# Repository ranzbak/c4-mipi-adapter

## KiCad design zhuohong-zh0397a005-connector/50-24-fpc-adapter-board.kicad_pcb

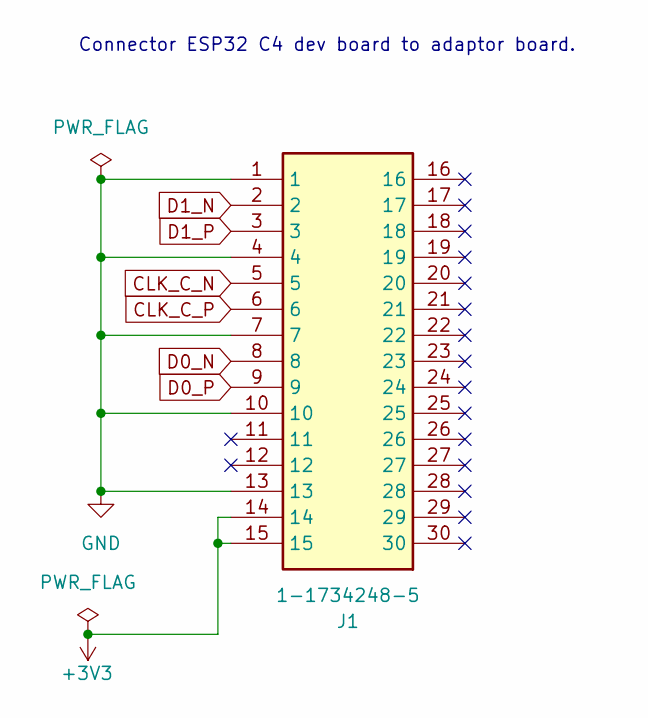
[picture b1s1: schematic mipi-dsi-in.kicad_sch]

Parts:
J1: 1-1734248-5; 117342485; Mouser Part Number 571-1-1734248-5

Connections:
+3V3: J1.14, J1.15; also elsewhere on the board
CLK_C_N: J1.5; also elsewhere on the board
CLK_C_P: J1.6; also elsewhere on the board
D0_N: J1.8; also elsewhere on the board
D0_P: J1.9; also elsewhere on the board
D1_N: J1.2; also elsewhere on the board
D1_P: J1.3; also elsewhere on the board
GND: J1.1, J1.4, J1.7, J1.10, J1.13; also elsewhere on the board

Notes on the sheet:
Connector ESP32 C4 dev board to adaptor board.

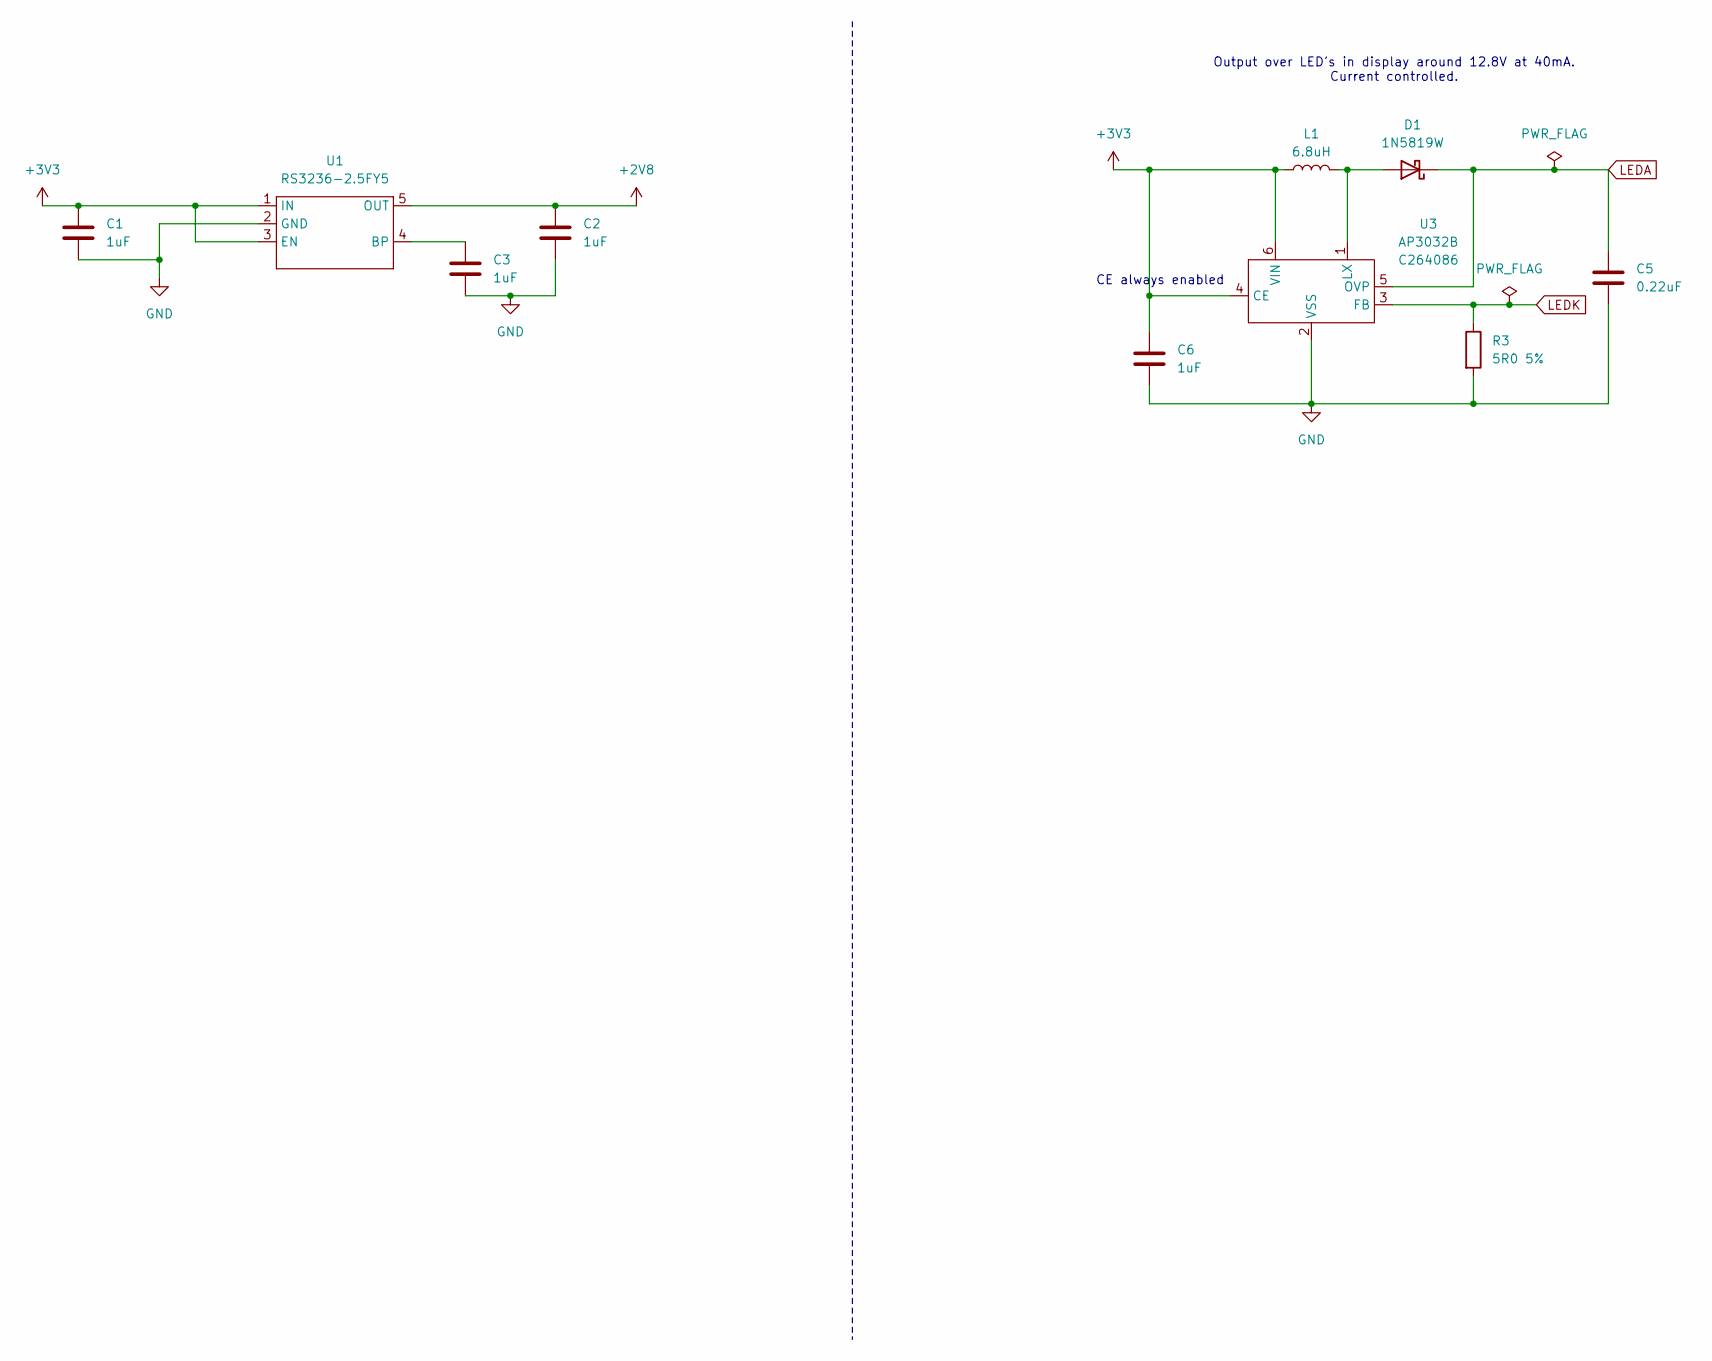
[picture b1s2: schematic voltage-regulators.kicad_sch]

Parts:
C1, C2, C3, C6: 1uF; C_0603_1608Metric; LCSC C386149
C5: 0.22uF; C_0603_1608Metric
D1: 1N5819W; D_SOD-123; LCSC C402219
L1: 6.8uH; L_1210_3225Metric; LCSC C394999
R3: 5R0 5%; R_0603_1608Metric; LCSC C2907176
U1: RS3236-2.5FY5; SOT-23-5; LCSC C379345
U3: AP3032B; SOT-23-6; LCSC C264086

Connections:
+2V8: C2.1, U1.5 (OUT); also elsewhere on the board
+3V3: C1.1, C6.1, L1.1, U1.1 (IN), U1.3 (EN), U3.4 (CE), U3.6 (VIN); also elsewhere on the board
GND: C1.2, C2.2, C3.2, C5.2, C6.2, R3.2, U1.2 (GND), U3.2 (VSS); also elsewhere on the board
LEDA: C5.1, D1.1 (K), U3.5 (OVP); also elsewhere on the board
LEDK: R3.1, U3.3 (FB); also elsewhere on the board
unnamed: D1.2 (A), L1.2, U3.1 (LX)
unnamed: C3.1, U1.4 (BP)

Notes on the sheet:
CE always enabled
Output over LED's in display around 12.8V at 40mA. Current controlled.

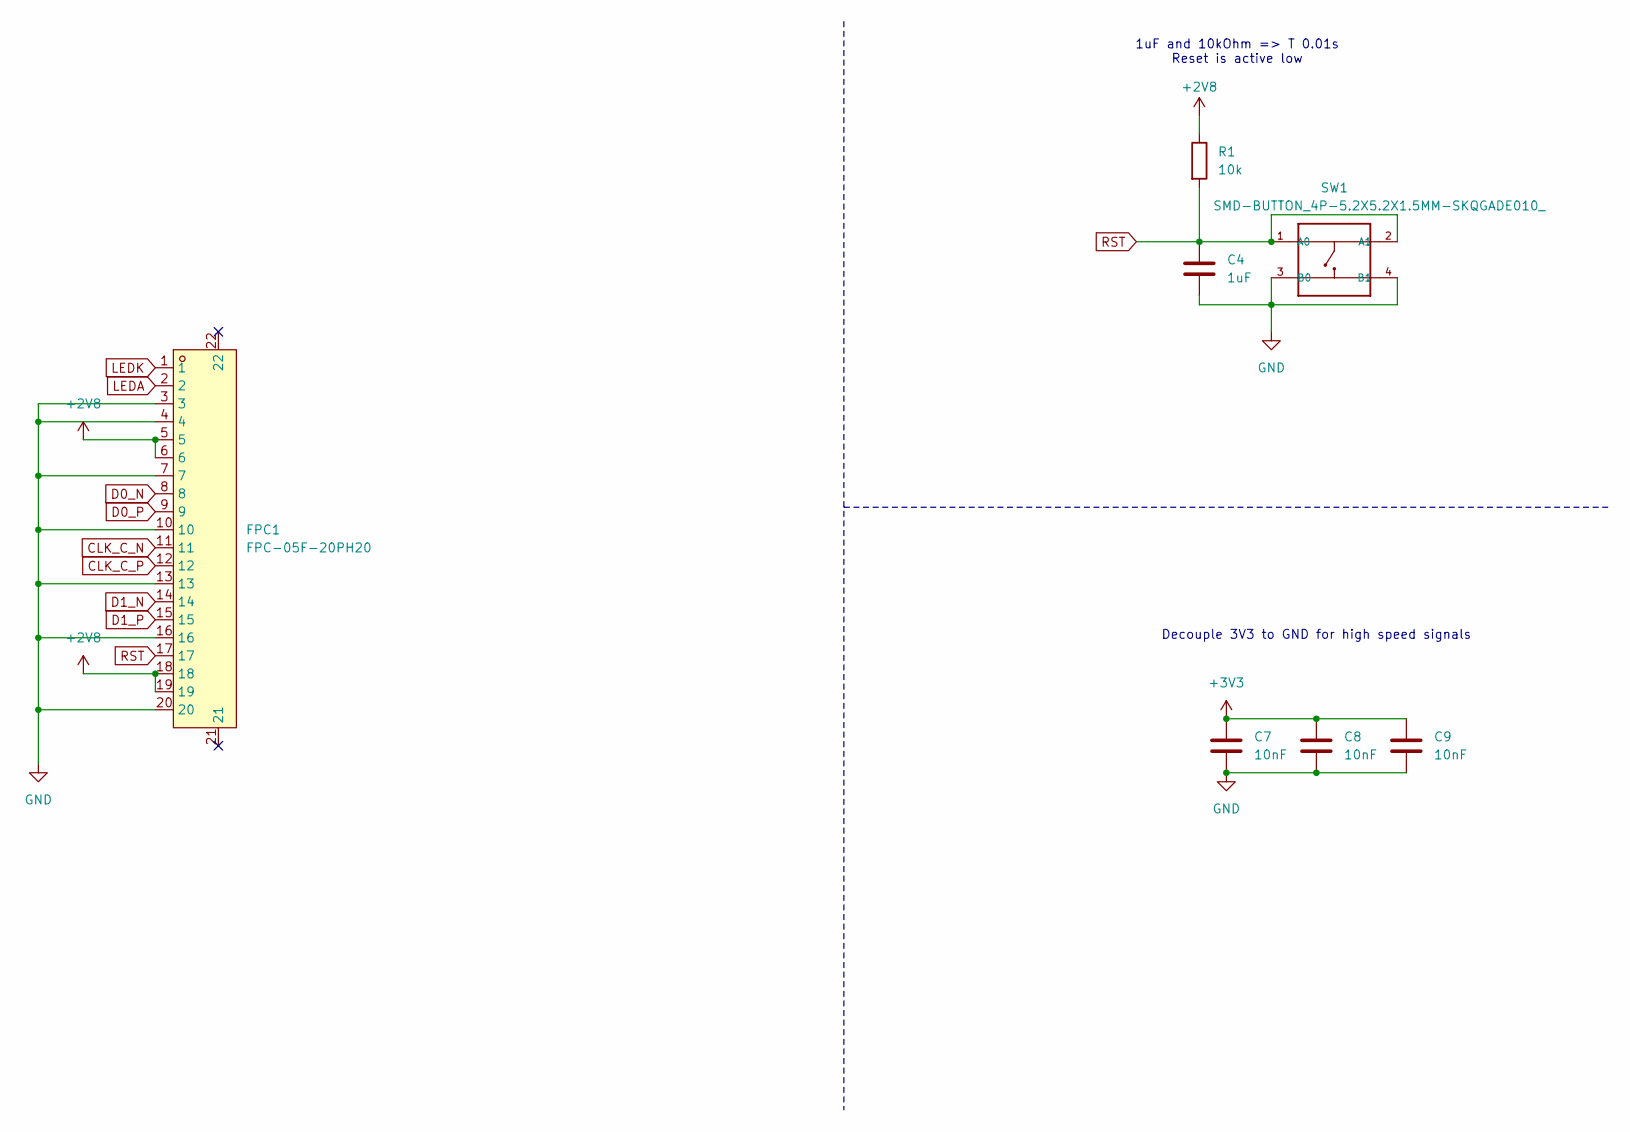
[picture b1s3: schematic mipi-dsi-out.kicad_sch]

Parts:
C4: 1uF; C_0603_1608Metric; LCSC C386149
C7, C8, C9: 10nF; C_0603_1608Metric; LCSC C525264
FPC1: FPC-05F-20PH20; FPC-SMD_20P-P0.50_XUNPU_FPC-05F-20PH20; LCSC C2856803
R1: 10k; R_0603_1608Metric; LCSC C2930027
SW1: SMD-BUTTON_4P-5.2X5.2X1.5MM-SKQGADE010_; SW4-SMD-5.2X5.2X1.5MM; LCSC C116647

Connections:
+2V8: FPC1.5, FPC1.6, FPC1.18, FPC1.19, R1.1; also elsewhere on the board
+3V3: C7.1, C8.1, C9.1; also elsewhere on the board
CLK_C_N: FPC1.11; also elsewhere on the board
CLK_C_P: FPC1.12; also elsewhere on the board
D0_N: FPC1.8; also elsewhere on the board
D0_P: FPC1.9; also elsewhere on the board
D1_N: FPC1.14; also elsewhere on the board
D1_P: FPC1.15; also elsewhere on the board
GND: C4.2, C7.2, C8.2, C9.2, FPC1.3, FPC1.4, FPC1.7, FPC1.10, FPC1.13, FPC1.16, FPC1.20, SW1.3 (B0), SW1.4 (B1); also elsewhere on the board
LEDA: FPC1.2; also elsewhere on the board
LEDK: FPC1.1; also elsewhere on the board
RST: C4.1, FPC1.17, R1.2, SW1.1 (A0), SW1.2 (A1)

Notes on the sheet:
1uF and 10kOhm => T 0.01s Reset is active low
Decouple 3V3 to GND for high speed signals

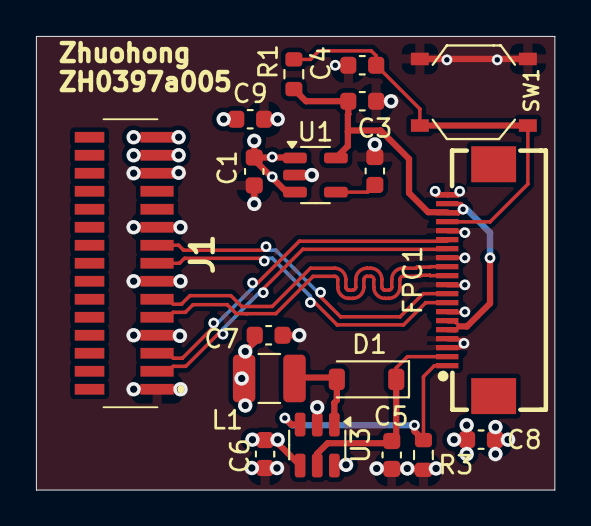
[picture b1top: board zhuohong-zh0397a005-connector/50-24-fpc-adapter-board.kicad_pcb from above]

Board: 4 copper layers, 28.8 x 25.2 mm, 18 parts (0 on the bottom side), 14 nets.

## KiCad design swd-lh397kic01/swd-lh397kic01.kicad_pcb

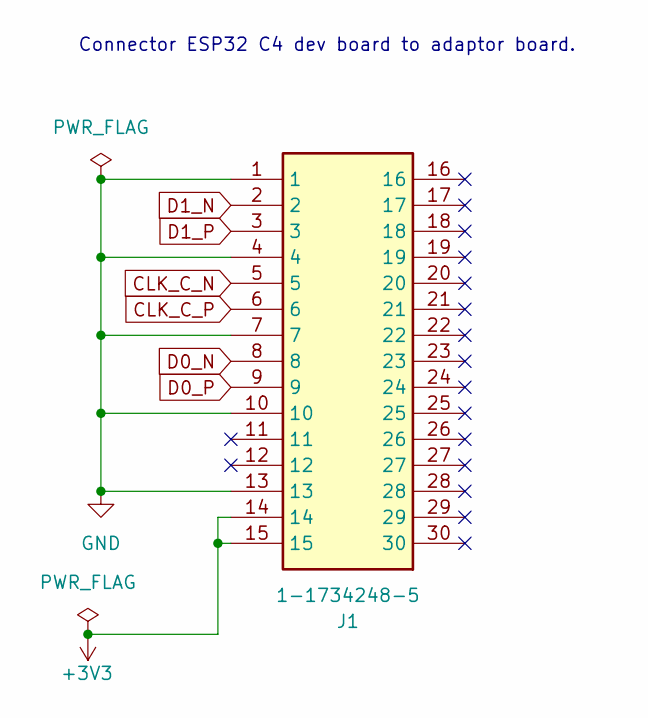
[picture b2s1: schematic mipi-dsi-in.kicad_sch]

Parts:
J1: 1-1734248-5; 117342485; Mouser Part Number 571-1-1734248-5

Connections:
+3V3: J1.14, J1.15; also elsewhere on the board
CLK_C_N: J1.5; also elsewhere on the board
CLK_C_P: J1.6; also elsewhere on the board
D0_N: J1.8; also elsewhere on the board
D0_P: J1.9; also elsewhere on the board
D1_N: J1.2; also elsewhere on the board
D1_P: J1.3; also elsewhere on the board
GND: J1.1, J1.4, J1.7, J1.10, J1.13; also elsewhere on the board

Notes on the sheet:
Connector ESP32 C4 dev board to adaptor board.

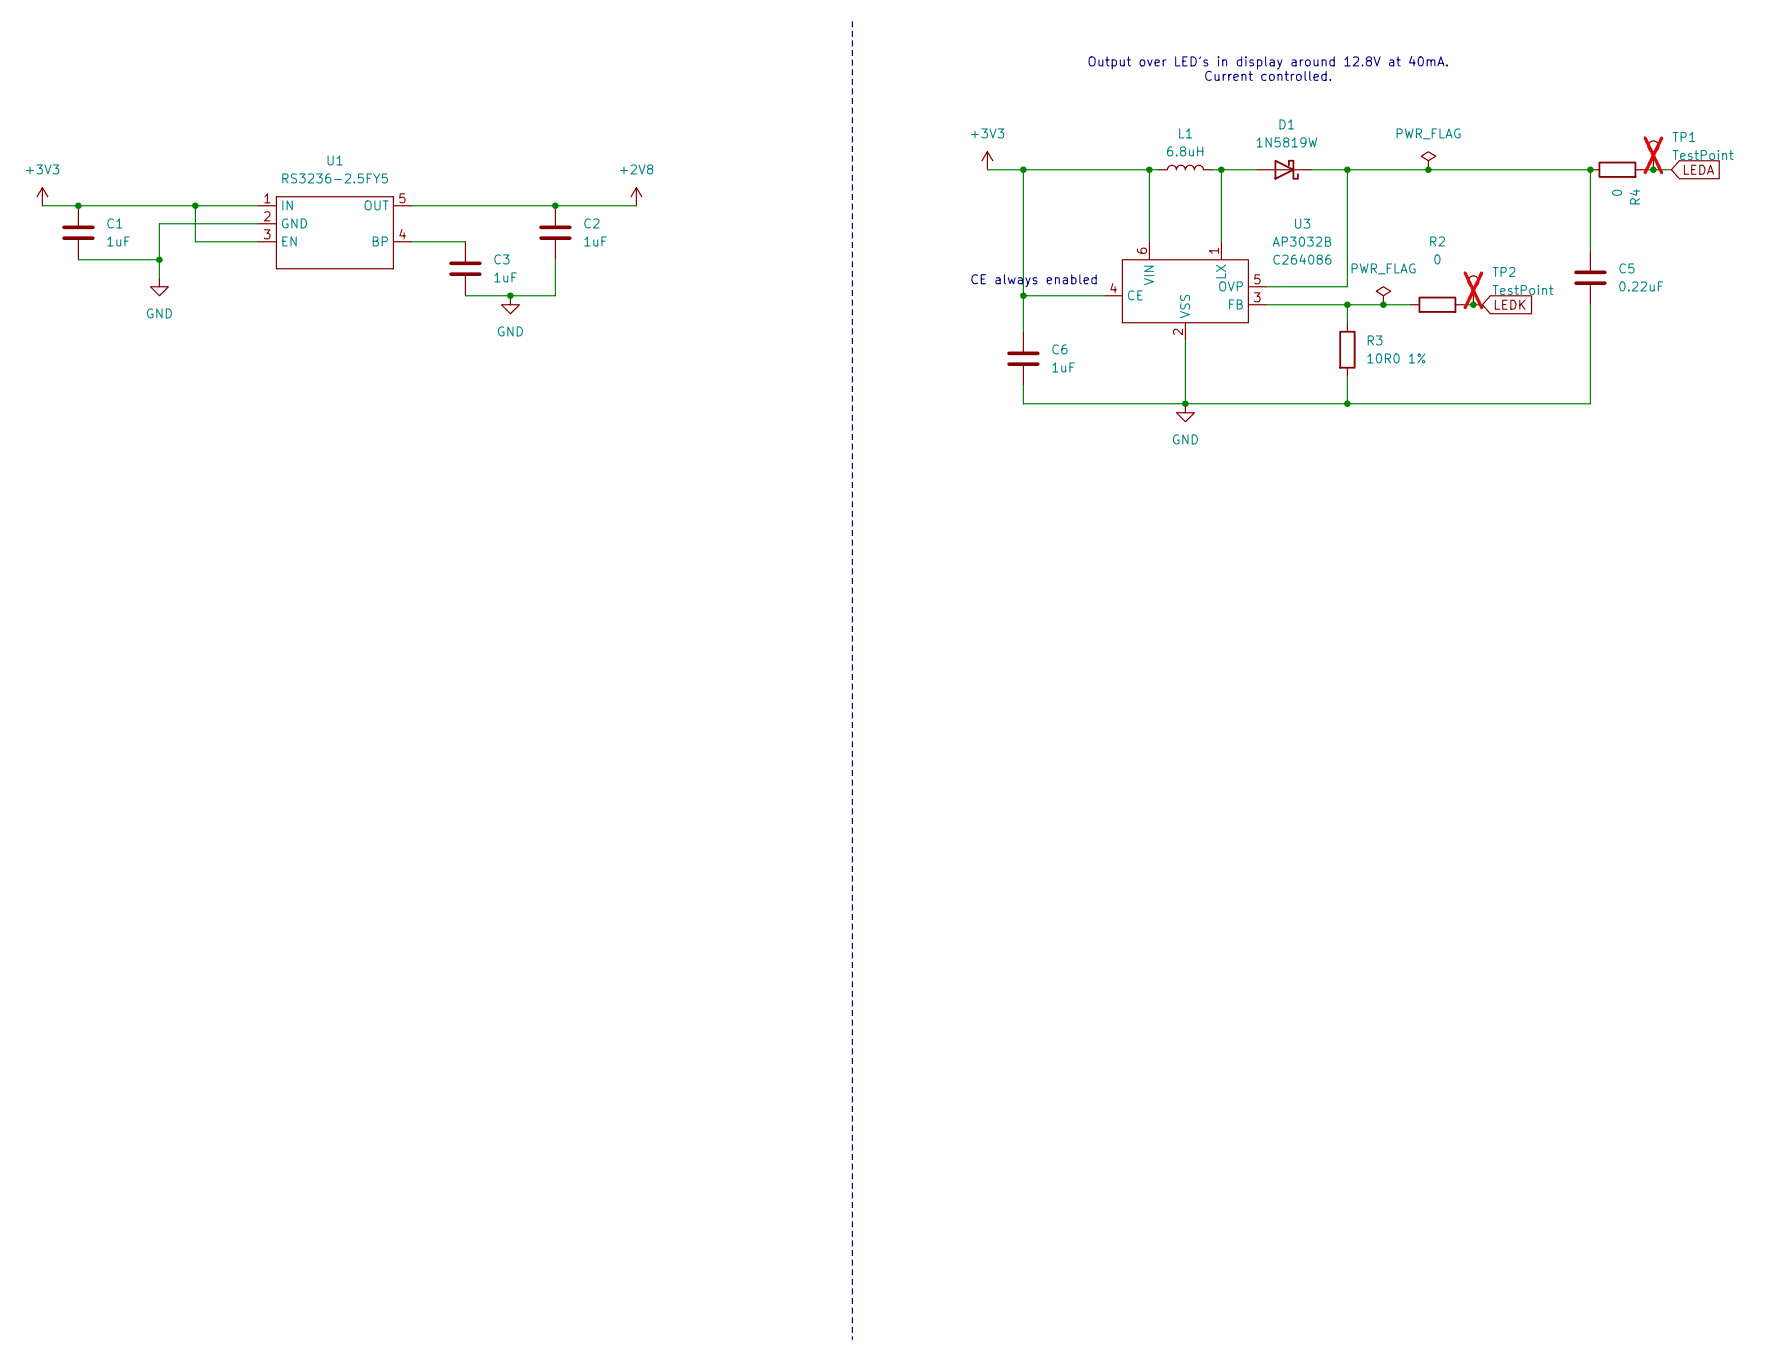
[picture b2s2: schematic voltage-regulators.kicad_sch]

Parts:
C1, C2, C3, C6: 1uF; C_0603_1608Metric; LCSC C386149
C5: 0.22uF; C_0603_1608Metric; LCSC C344195
D1: 1N5819W; D_SOD-123; LCSC C402219
L1: 6.8uH; L_1210_3225Metric_Pad1.42x2.65mm_HandSolder; LCSC C394999
R2, R4: 0; R_0603_1608Metric; LCSC C3016185
R3: 10R0 1%; R_0603_1608Metric; LCSC C103222
TP1, TP2: TestPoint; TestPoint_Pad_D1.0mm; not fitted
U1: RS3236-2.5FY5; SOT-23-5; LCSC C379345
U3: AP3032B; SOT-23-6; LCSC C264086

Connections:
+2V8: C2.1, U1.5 (OUT); also elsewhere on the board
+3V3: C1.1, C6.1, L1.1, U1.1 (IN), U1.3 (EN), U3.4 (CE), U3.6 (VIN); also elsewhere on the board
GND: C1.2, C2.2, C3.2, C5.2, C6.2, R3.2, U1.2 (GND), U3.2 (VSS); also elsewhere on the board
LEDA: R4.2, TP1.1; also elsewhere on the board
LEDK: R2.2, TP2.1; also elsewhere on the board
unnamed: D1.2 (A), L1.2, U3.1 (LX)
unnamed: C5.1, D1.1 (K), R4.1, U3.5 (OVP)
unnamed: C3.1, U1.4 (BP)
unnamed: R2.1, R3.1, U3.3 (FB)

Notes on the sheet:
CE always enabled
Output over LED's in display around 12.8V at 40mA. Current controlled.

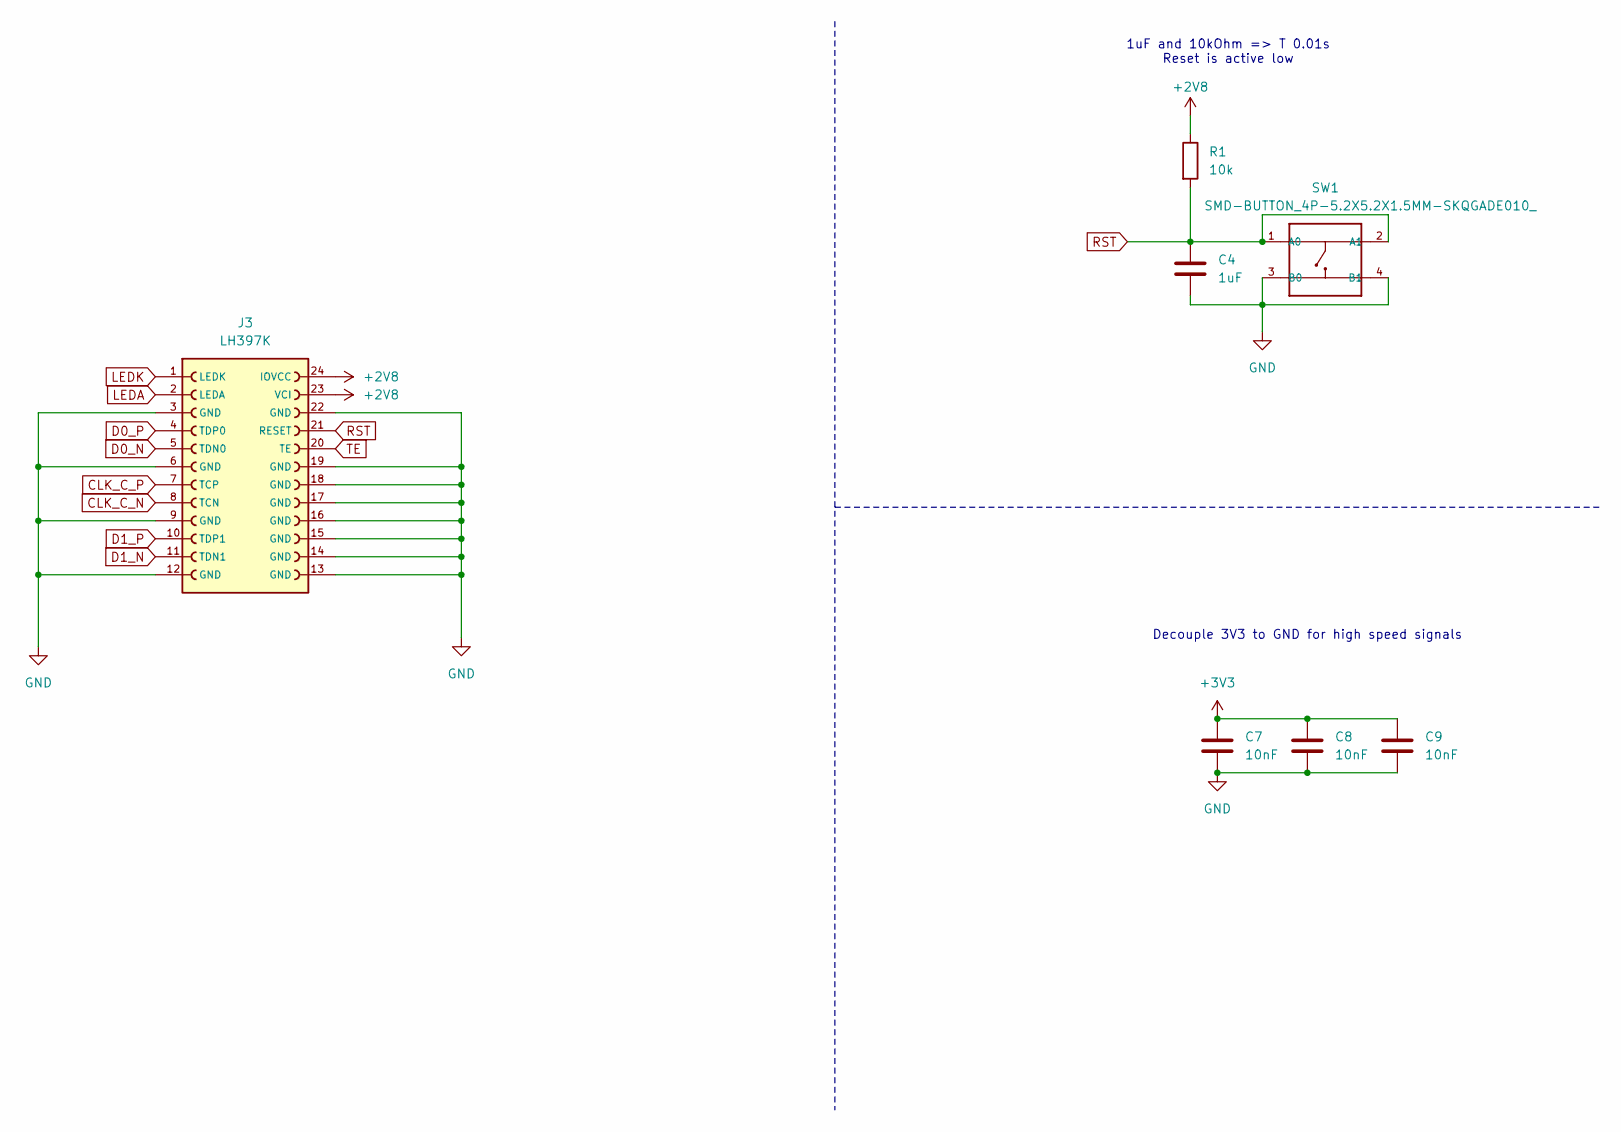
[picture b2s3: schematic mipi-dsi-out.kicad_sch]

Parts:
C4: 1uF; C_0603_1608Metric; LCSC C386149
C7, C8, C9: 10nF; C_0603_1608Metric; LCSC C525264
J3: LH397K; LH397K-IC01
R1: 10k; R_0603_1608Metric; LCSC C2930027
SW1: SMD-BUTTON_4P-5.2X5.2X1.5MM-SKQGADE010_; SW4-SMD-5.2X5.2X1.5MM; LCSC C116647

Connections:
+2V8: J3.23 (VCI), J3.24 (IOVCC), R1.1; also elsewhere on the board
+3V3: C7.1, C8.1, C9.1; also elsewhere on the board
CLK_C_N: J3.8 (TCN); also elsewhere on the board
CLK_C_P: J3.7 (TCP); also elsewhere on the board
D0_N: J3.5 (TDN0); also elsewhere on the board
D0_P: J3.4 (TDP0); also elsewhere on the board
D1_N: J3.11 (TDN1); also elsewhere on the board
D1_P: J3.10 (TDP1); also elsewhere on the board
GND: C4.2, C7.2, C8.2, C9.2, J3.3 (GND), J3.6 (GND), J3.9 (GND), J3.12 (GND), J3.13 (GND), J3.14 (GND), J3.15 (GND), J3.16 (GND), J3.17 (GND), J3.18 (GND), J3.19 (GND), J3.22 (GND), SW1.3 (B0), SW1.4 (B1); also elsewhere on the board
LEDA: J3.2 (LEDA); also elsewhere on the board
LEDK: J3.1 (LEDK); also elsewhere on the board
RST: C4.1, J3.21 (RESET), R1.2, SW1.1 (A0), SW1.2 (A1)
TE: J3.20 (TE)

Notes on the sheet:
1uF and 10kOhm => T 0.01s Reset is active low
Decouple 3V3 to GND for high speed signals

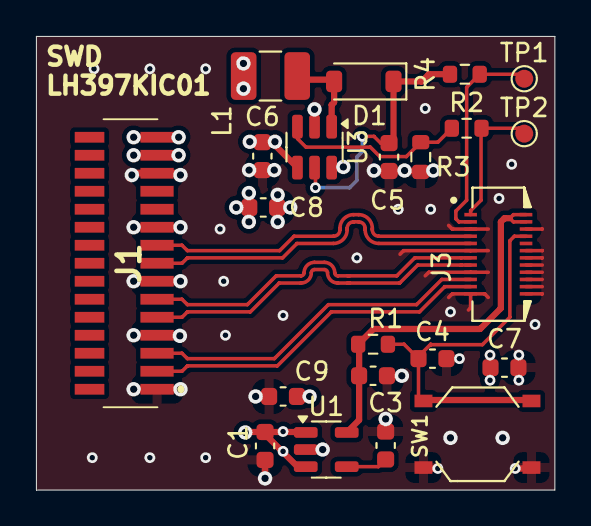
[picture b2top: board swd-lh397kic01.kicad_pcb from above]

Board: 4 copper layers, 28.8 x 25.2 mm, 22 parts (0 on the bottom side), 16 nets.

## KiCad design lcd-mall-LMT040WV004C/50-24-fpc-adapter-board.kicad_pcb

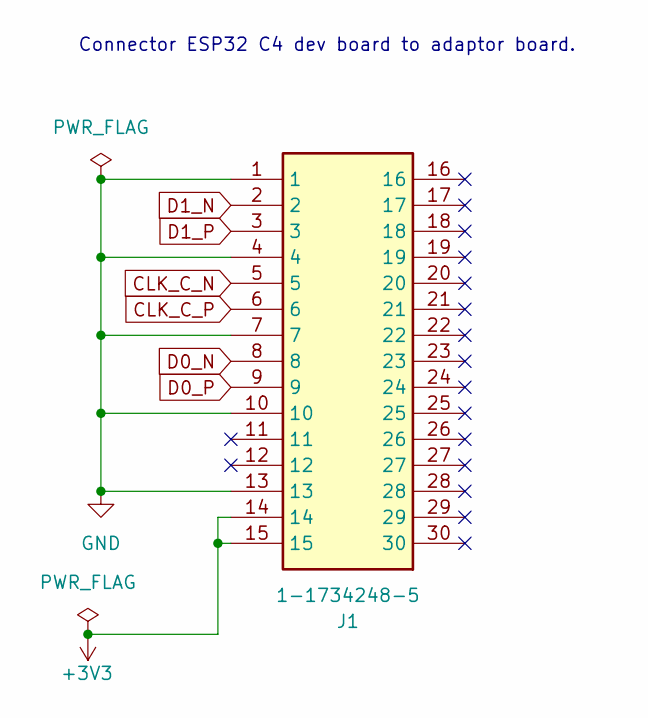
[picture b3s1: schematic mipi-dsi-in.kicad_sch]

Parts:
J1: 1-1734248-5; 117342485; Mouser Part Number 571-1-1734248-5

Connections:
+3V3: J1.14, J1.15; also elsewhere on the board
CLK_C_N: J1.5; also elsewhere on the board
CLK_C_P: J1.6; also elsewhere on the board
D0_N: J1.8; also elsewhere on the board
D0_P: J1.9; also elsewhere on the board
D1_N: J1.2; also elsewhere on the board
D1_P: J1.3; also elsewhere on the board
GND: J1.1, J1.4, J1.7, J1.10, J1.13; also elsewhere on the board

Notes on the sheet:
Connector ESP32 C4 dev board to adaptor board.

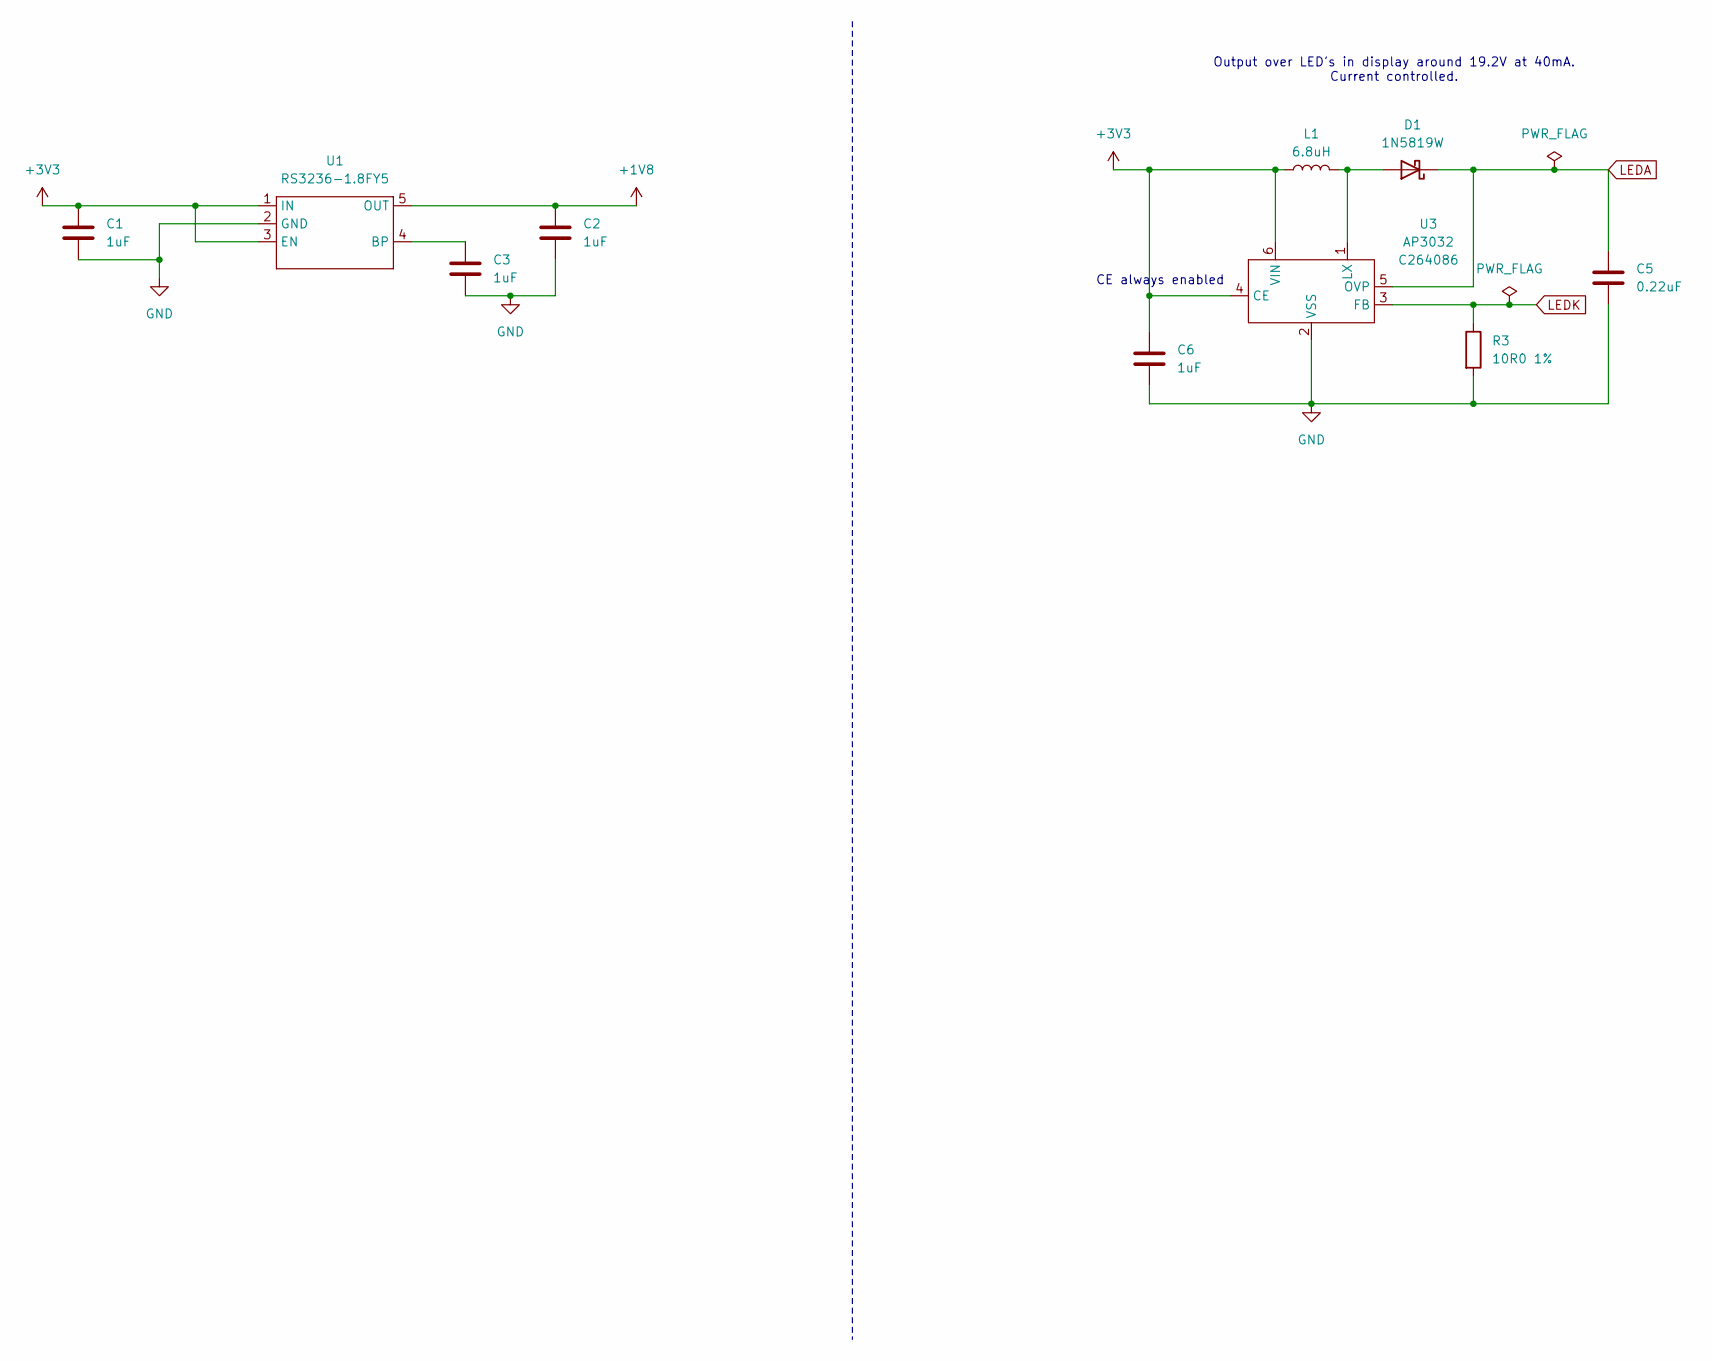
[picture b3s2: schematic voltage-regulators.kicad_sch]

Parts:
C1, C2, C3, C6: 1uF; C_0603_1608Metric; LCSC C126631
C5: 0.22uF; C_0603_1608Metric
D1: 1N5819W; D_SOD-123; LCSC C402219
L1: 6.8uH; L_1210_3225Metric; LCSC C394999
R3: 10R0 1%; R_0603_1608Metric; LCSC C103222
U1: RS3236-1.8FY5; SOT-23-5; LCSC C379345
U3: AP3032; SOT-23-6; LCSC C264086

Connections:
+1V8: C2.1, U1.5 (OUT); also elsewhere on the board
+3V3: C1.1, C6.1, L1.1, U1.1 (IN), U1.3 (EN), U3.4 (CE), U3.6 (VIN); also elsewhere on the board
GND: C1.2, C2.2, C3.2, C5.2, C6.2, R3.2, U1.2 (GND), U3.2 (VSS); also elsewhere on the board
LEDA: C5.1, D1.1 (K), U3.5 (OVP); also elsewhere on the board
LEDK: R3.1, U3.3 (FB); also elsewhere on the board
unnamed: D1.2 (A), L1.2, U3.1 (LX)
unnamed: C3.1, U1.4 (BP)

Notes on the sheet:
CE always enabled
Output over LED's in display around 19.2V at 40mA. Current controlled.

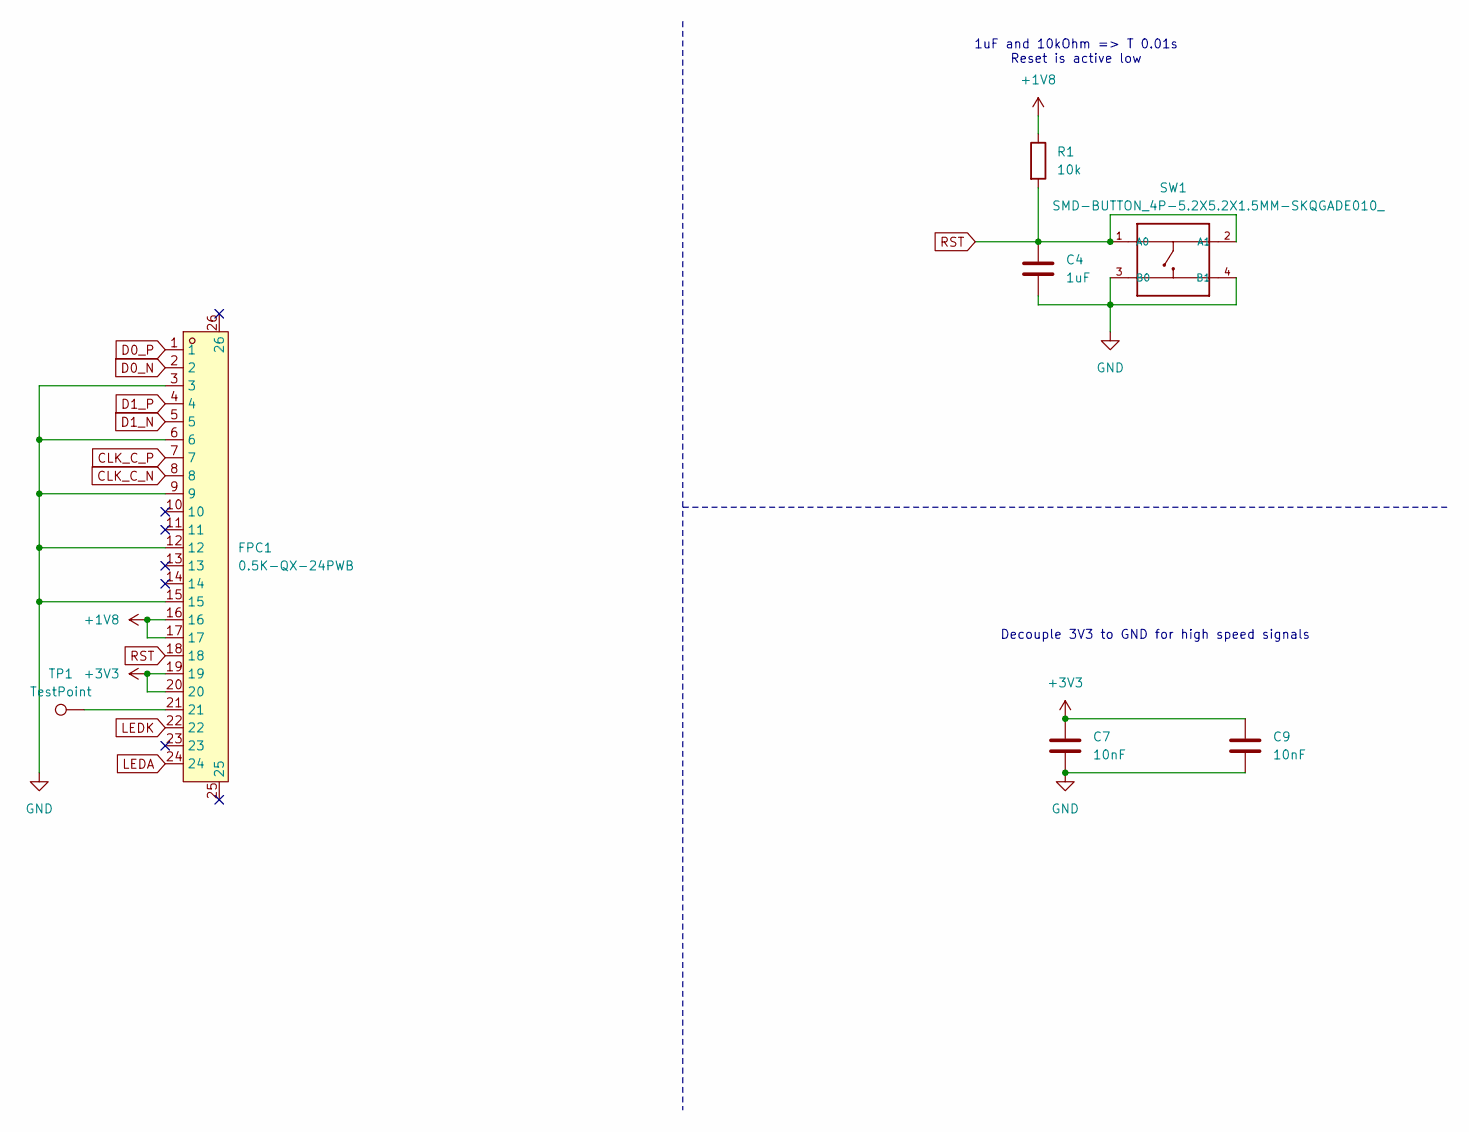
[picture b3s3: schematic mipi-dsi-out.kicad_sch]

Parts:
C4: 1uF; C_0603_1608Metric; LCSC C126631
C7, C9: 10nF; C_0603_1608Metric; LCSC C525264
FPC1: 0.5K-QX-24PWB; FPC-SMD_24P-P0.50_HDGC_0.5K-QX-24PWB; LCSC Part C2919484
R1: 10k; R_0603_1608Metric; LCSC C2930027
SW1: SMD-BUTTON_4P-5.2X5.2X1.5MM-SKQGADE010_; SW4-SMD-5.2X5.2X1.5MM; LCSC C116647
TP1: TestPoint; TestPoint_Pad_D1.0mm

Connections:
+1V8: FPC1.16, FPC1.17, R1.1; also elsewhere on the board
+3V3: C7.1, C9.1, FPC1.19, FPC1.20; also elsewhere on the board
CLK_C_N: FPC1.8; also elsewhere on the board
CLK_C_P: FPC1.7; also elsewhere on the board
D0_N: FPC1.2; also elsewhere on the board
D0_P: FPC1.1; also elsewhere on the board
D1_N: FPC1.5; also elsewhere on the board
D1_P: FPC1.4; also elsewhere on the board
GND: C4.2, C7.2, C9.2, FPC1.3, FPC1.6, FPC1.9, FPC1.12, FPC1.15, SW1.3 (B0), SW1.4 (B1); also elsewhere on the board
LEDA: FPC1.24; also elsewhere on the board
LEDK: FPC1.22; also elsewhere on the board
unnamed: FPC1.21, TP1.1
RST: C4.1, FPC1.18, R1.2, SW1.1 (A0), SW1.2 (A1)

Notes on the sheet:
1uF and 10kOhm => T 0.01s Reset is active low
Decouple 3V3 to GND for high speed signals

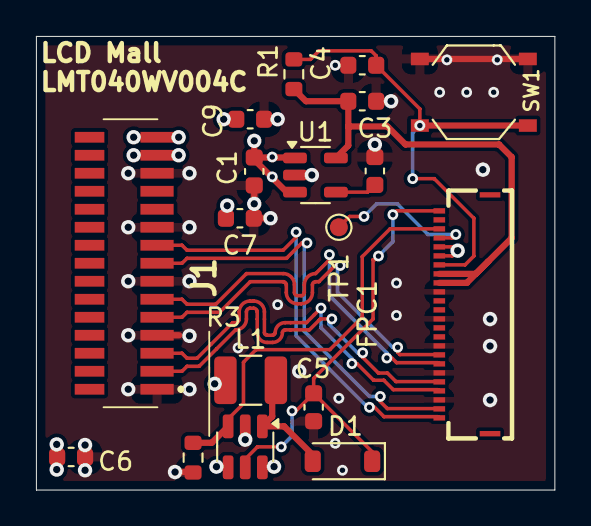
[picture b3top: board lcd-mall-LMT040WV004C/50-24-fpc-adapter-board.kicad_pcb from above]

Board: 4 copper layers, 28.8 x 25.2 mm, 18 parts (0 on the bottom side), 15 nets.

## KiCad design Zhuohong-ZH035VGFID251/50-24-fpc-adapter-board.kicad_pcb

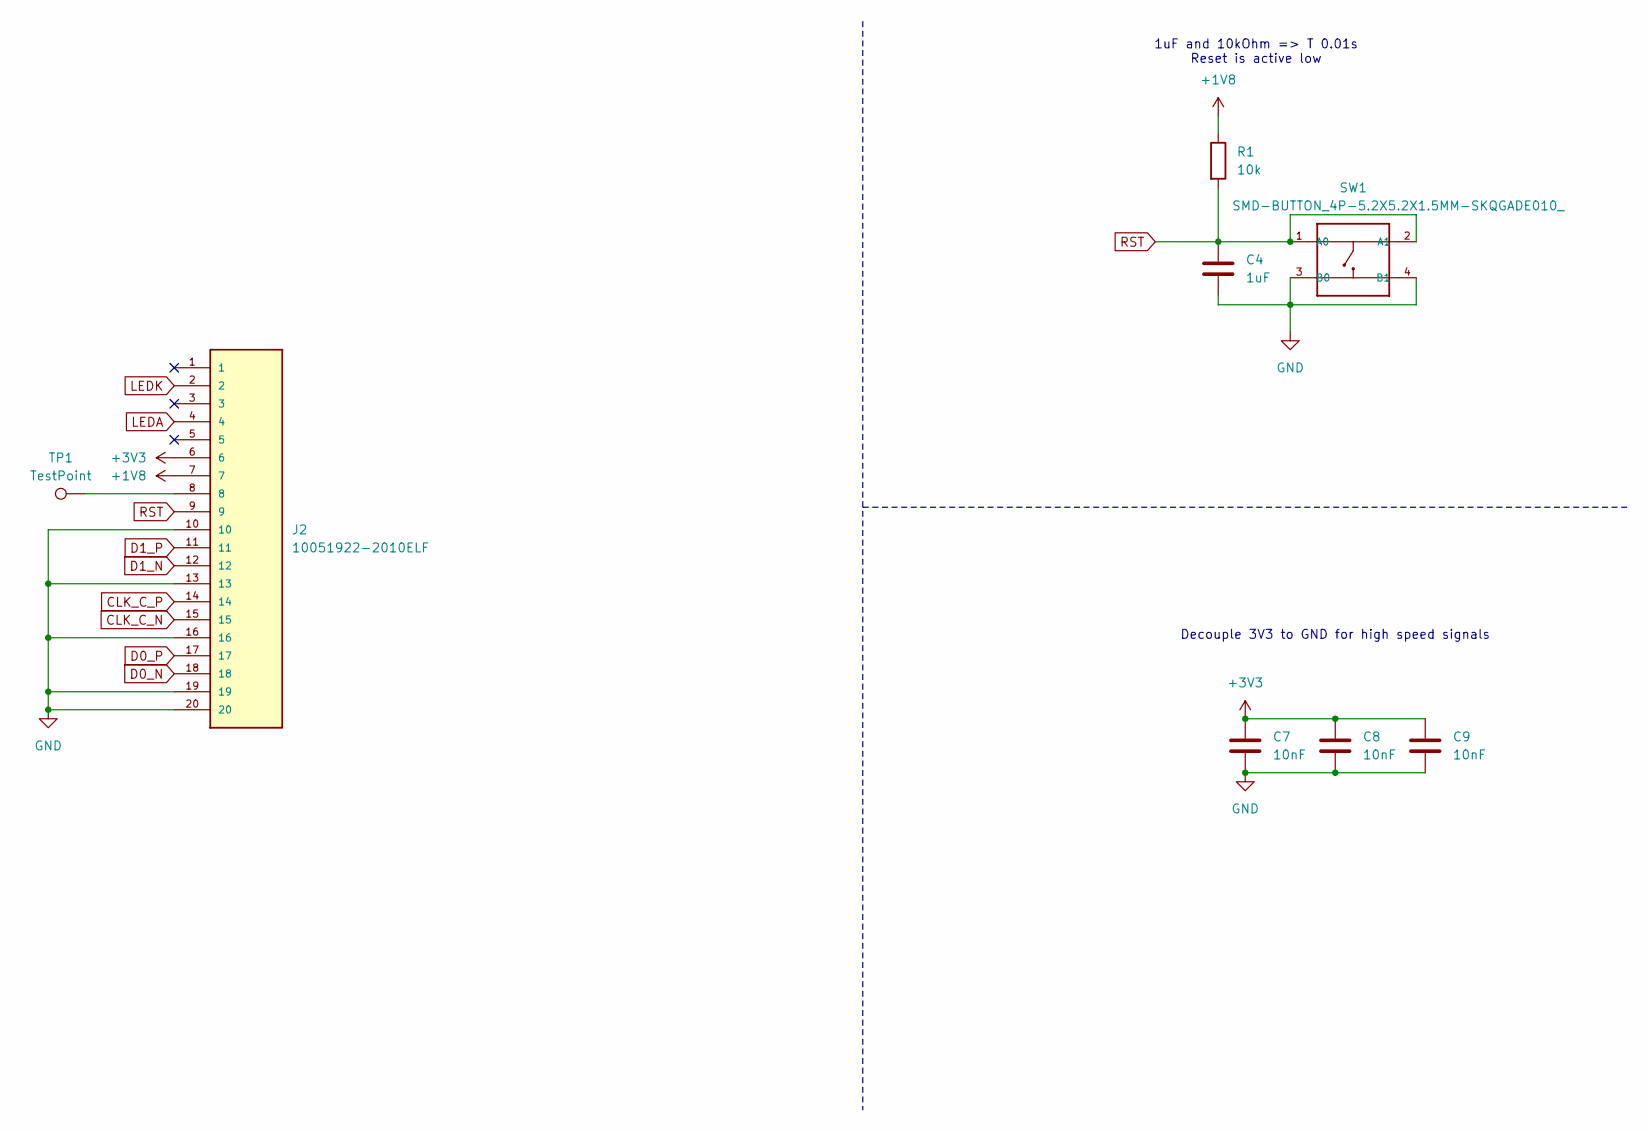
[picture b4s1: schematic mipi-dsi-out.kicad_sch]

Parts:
C4: 1uF; C_0603_1608Metric; LCSC C5189821
C7, C8, C9: 10nF; C_0603_1608Metric; LCSC C525264
J2: 10051922-2010ELF; AMPHENOL_10051922-2010ELF; PARTREV K; LCSC C3169799
R1: 10k; R_0603_1608Metric; LCSC C2930027
SW1: SMD-BUTTON_4P-5.2X5.2X1.5MM-SKQGADE010_; SW4-SMD-5.2X5.2X1.5MM; LCSC C116647
TP1: TestPoint; TestPoint_Pad_D1.0mm

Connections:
+1V8: J2.7, R1.1; also elsewhere on the board
+3V3: C7.1, C8.1, C9.1, J2.6; also elsewhere on the board
CLK_C_N: J2.15; also elsewhere on the board
CLK_C_P: J2.14; also elsewhere on the board
D0_N: J2.18; also elsewhere on the board
D0_P: J2.17; also elsewhere on the board
D1_N: J2.12; also elsewhere on the board
D1_P: J2.11; also elsewhere on the board
GND: C4.2, C7.2, C8.2, C9.2, J2.10, J2.13, J2.16, J2.19, J2.20, SW1.3 (B0), SW1.4 (B1); also elsewhere on the board
LEDA: J2.4; also elsewhere on the board
LEDK: J2.2; also elsewhere on the board
unnamed: J2.8, TP1.1
RST: C4.1, J2.9, R1.2, SW1.1 (A0), SW1.2 (A1)

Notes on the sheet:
1uF and 10kOhm => T 0.01s Reset is active low
Decouple 3V3 to GND for high speed signals
